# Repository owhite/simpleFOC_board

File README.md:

# Clone your repo (if you don’t already have it locally)
git clone https://github.com/owhite/simpleFOC_board.git

cd simpleFOC_board

# Make sure you have the latest tags
git fetch --tags

# Check out the tag you want
git checkout jlcpcb-order-Y34-4852697

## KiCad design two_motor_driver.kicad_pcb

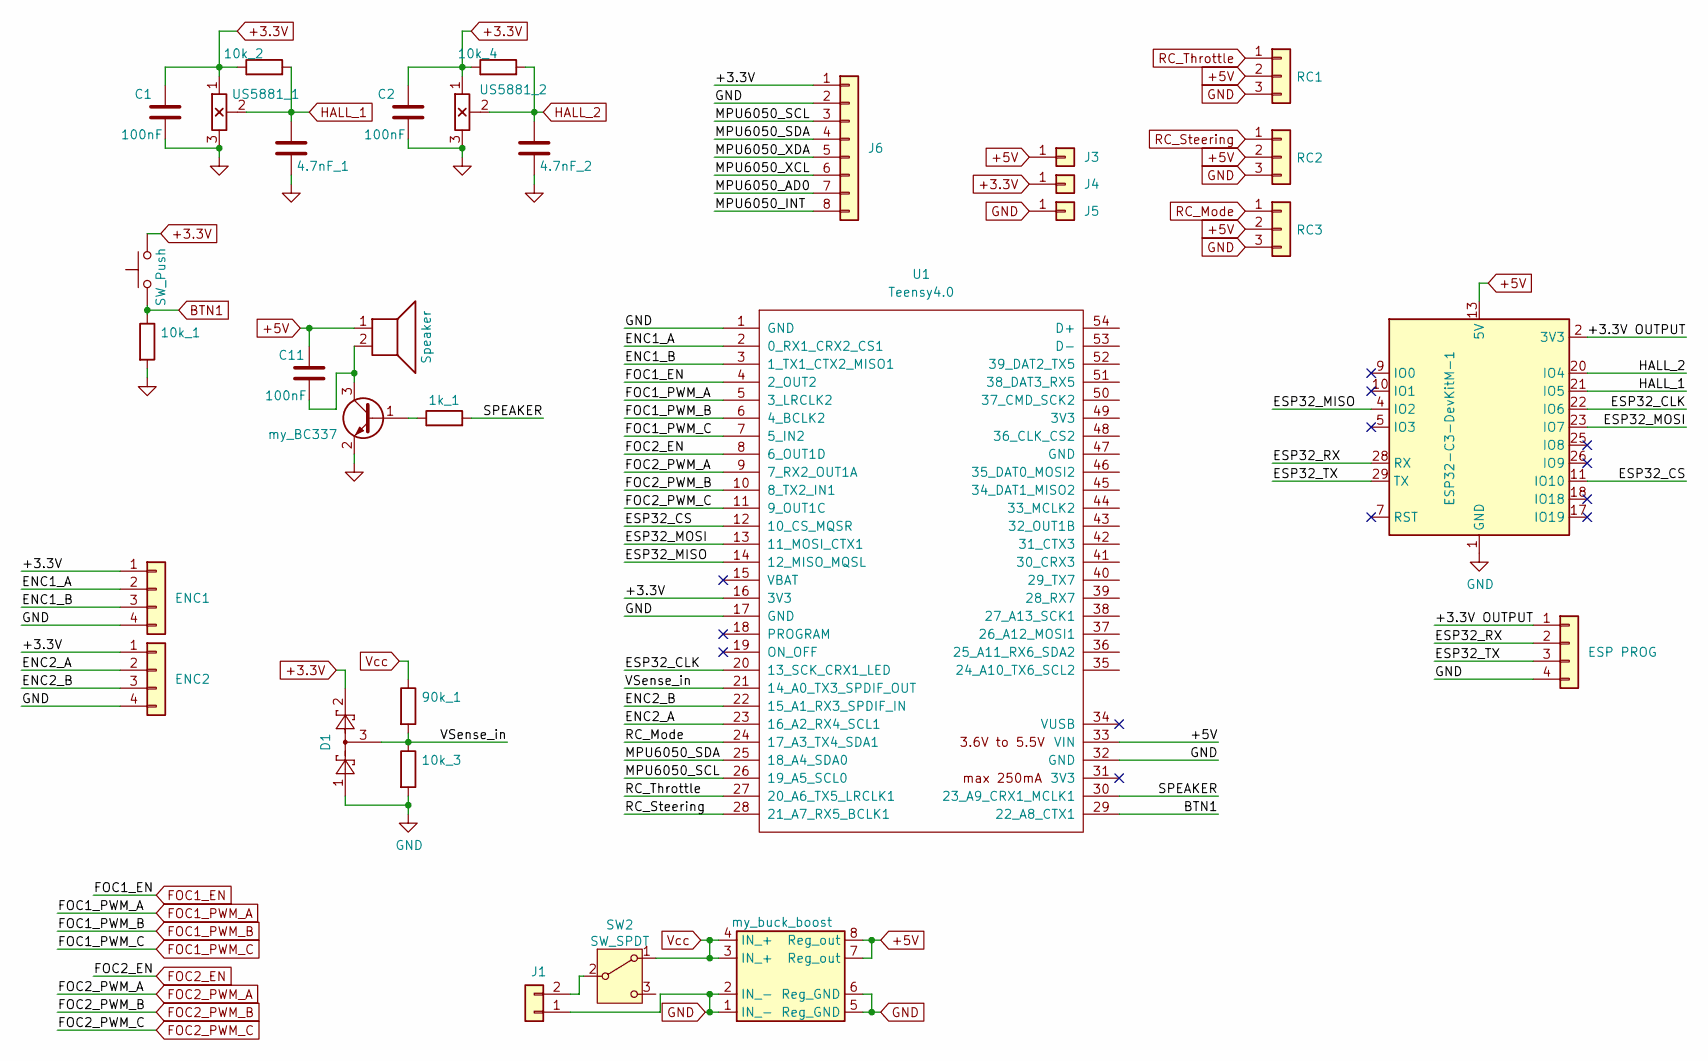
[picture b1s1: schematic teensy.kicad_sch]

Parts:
1k_1, 10k_1, 10k_2, 10k_3, 10k_4: 10k; R_0805_2012Metric
4.7nF_1, 4.7nF_2: 4.7nF; C_0805_2012Metric
90k_1: 90k; R_0805_2012Metric
C1, C2, C11: 100nF; C_0805_2012Metric
D1: BAT54S; SOT-23-3
ENC1, ENC2: J1; PinSocket_1x04_P2.54mm_Vertical
J1: Conn_01x02; PinHeader_1x02_P2.54mm_Vertical
J2: ESP PROG; PinSocket_1x04_P2.54mm_Vertical
J3, J4, J5: Conn_01x01; PinSocket_1x01_P2.54mm_Vertical
J6: Conn_01x08; PinSocket_1x08_P2.54mm_Vertical
LS1: Speaker; SPKR_CDS-13138-SMT-TR
Q2: my_BC337; SOT-23
RC1, RC2, RC3: Conn_01x03; PinHeader_1x03_P2.54mm_Vertical
SW1: SW_Push; SW_Push_SPST_NO_Alps_SKRK
SW2: SW_SPDT; SW_NKK_BB15AH
U1: Teensy4.0; Teensy40
U2: ESP32-C3-DevKitM-1
U5: my_buck_boost
US5881_1, US5881_2: hall_effect_three_wire; PinHeader_1x03_P2.54mm_Vertical

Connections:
+3.3V: 10k_2.1, 10k_4.1, C1.1, C2.1, D1.2, ENC1.1, ENC2.1, J4.1, J6.1, SW1.2, U1.16 (3V3), US5881_1.1 (V+), US5881_2.1 (V+); also elsewhere on the board
+5V: C11.1, J3.1, LS1.1, RC1.2, RC2.2, RC3.2, U1.33 (VIN), U2.13 (5V), U2.14 (5V), U5.7 (Reg_out), U5.8 (Reg_out)
/teensy/+3.3V OUTPUT: J2.1, U2.2 (3V3), U2.3 (3V3)
/teensy/ENC1_A: ENC1.2, U1.2 (0_RX1_CRX2_CS1)
/teensy/ENC1_B: ENC1.3, U1.3 (1_TX1_CTX2_MISO1)
/teensy/ENC2_A: ENC2.2, U1.23 (16_A2_RX4_SCL1)
/teensy/ENC2_B: ENC2.3, U1.22 (15_A1_RX3_SPDIF_IN)
/teensy/ESP32_CLK: U1.20 (13_SCK_CRX1_LED), U2.22 (IO6)
/teensy/ESP32_CS: U1.12 (10_CS_MQSR), U2.11 (IO10)
/teensy/ESP32_MISO: U1.14 (12_MISO_MQSL), U2.4 (IO2)
/teensy/ESP32_MOSI: U1.13 (11_MOSI_CTX1), U2.23 (IO7)
/teensy/ESP32_RX: J2.2, U2.28 (RX)
/teensy/ESP32_TX: J2.3, U2.29 (TX)
/teensy/MPU6050_AD0: J6.7
/teensy/MPU6050_INT: J6.8
/teensy/MPU6050_SCL: J6.3, U1.26 (19_A5_SCL0)
/teensy/MPU6050_SDA: J6.4, U1.25 (18_A4_SDA0)
/teensy/MPU6050_XCL: J6.6
/teensy/MPU6050_XDA: J6.5
/teensy/SPEAKER: 1k_1.2, U1.30 (23_A9_CRX1_MCLK1)
/teensy/VSense_in: 10k_3.1, 90k_1.2, D1.3, U1.21 (14_A0_TX3_SPDIF_OUT)
BTN1: 10k_1.1, SW1.1, U1.29 (22_A8_CTX1)
FOC1_EN: U1.4 (2_OUT2); also elsewhere on the board
FOC1_PWM_A: U1.5 (3_LRCLK2); also elsewhere on the board
FOC1_PWM_B: U1.6 (4_BCLK2); also elsewhere on the board
FOC1_PWM_C: U1.7 (5_IN2); also elsewhere on the board
FOC2_EN: U1.8 (6_OUT1D); also elsewhere on the board
FOC2_PWM_A: U1.9 (7_RX2_OUT1A); also elsewhere on the board
FOC2_PWM_B: U1.10 (8_TX2_IN1); also elsewhere on the board
FOC2_PWM_C: U1.11 (9_OUT1C); also elsewhere on the board
GND: 4.7nF_1.2, 4.7nF_2.2, 10k_1.2, 10k_3.2, C1.2, C2.2, D1.1, ENC1.4, ENC2.4, J1.1, J2.4, J5.1, J6.2, Q2.2 (E), RC1.3, RC2.3, RC3.3, U1.1 (GND), U1.17 (GND), U1.32 (GND), U2.1 (GND), U2.6 (GND), U2.8 (GND), U2.12 (GND), U2.15 (GND), U2.16 (GND), U2.19 (GND), U2.24 (GND), U2.27 (GND), U2.30 (GND), U5.1 (IN_-), U5.2 (IN_-), U5.5 (Reg_GND), U5.6 (Reg_GND), US5881_1.3 (V-), US5881_2.3 (V-); also elsewhere on the board
HALL_1: 4.7nF_1.1, 10k_2.2, U2.21 (IO5), US5881_1.2 (out)
HALL_2: 4.7nF_2.1, 10k_4.2, U2.20 (IO4), US5881_2.2 (out)
unnamed: J1.2, SW2.2 (B)
unnamed: 1k_1.1, Q2.1 (B)
unnamed: C11.2, LS1.2, Q2.3 (C)
RC_Mode: RC3.1, U1.24 (17_A3_TX4_SDA1)
RC_Steering: RC2.1, U1.28 (21_A7_RX5_BCLK1)
RC_Throttle: RC1.1, U1.27 (20_A6_TX5_LRCLK1)
Vcc: 90k_1.1, SW2.1 (A), U5.3 (IN_+), U5.4 (IN_+); also elsewhere on the board

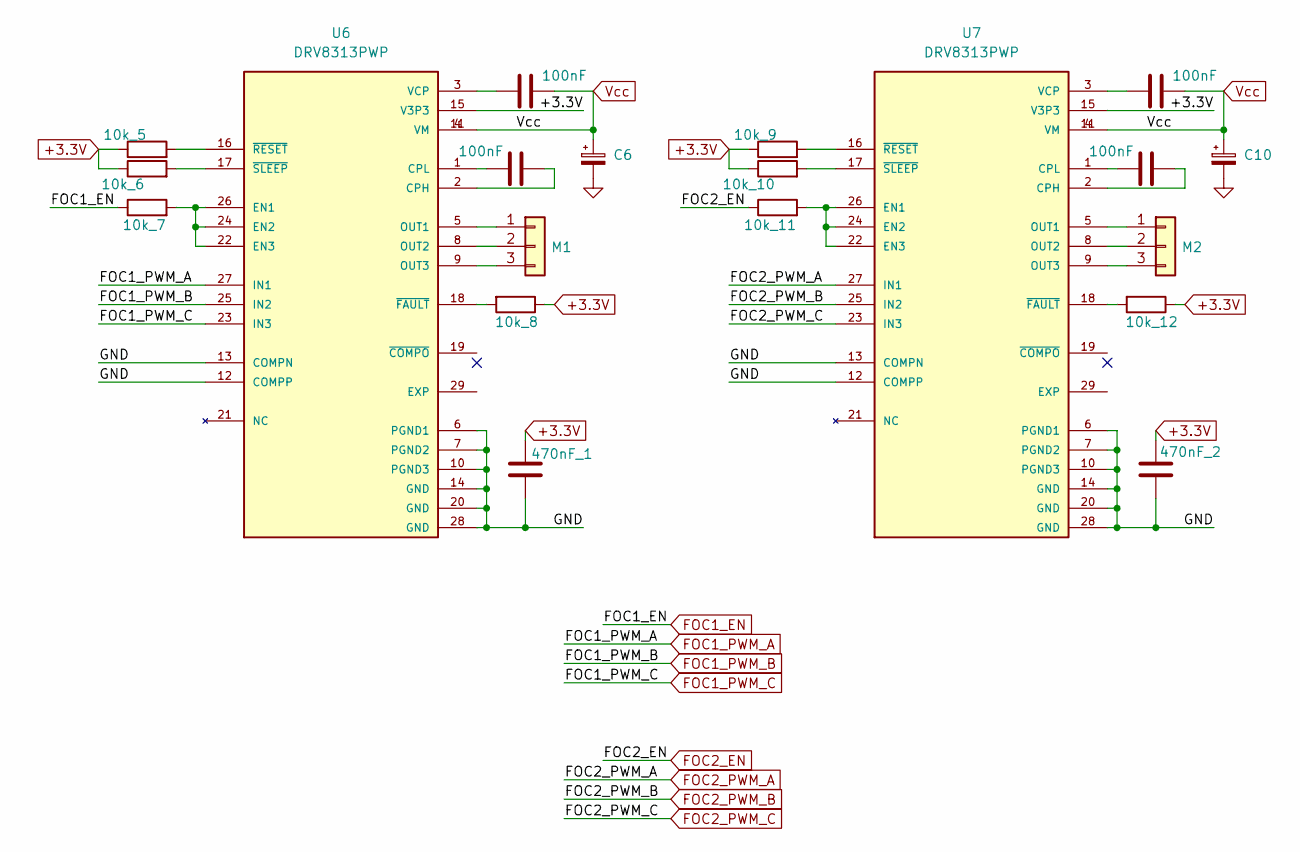
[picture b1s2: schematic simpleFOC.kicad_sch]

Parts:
10k_5, 10k_6, 10k_8, 10k_9, 10k_10, 10k_11, 10k_12: 10k; R_0805_2012Metric
10k_7: 10k; R_0603_1608Metric
470nF_1, 470nF_2: 470nF; C_0805_2012Metric
C3, C4, C7, C8: 100nF; C_0805_2012Metric
C6, C10: C_Polarized_Small; CAP-SMD_BD6.3-L6.6-W6.6-FD
M1, M2: Conn_01x03; PinHeader_1x03_P2.54mm_Vertical
U6, U7: DRV8313PWP; SOP65P640X120-29N; PARTREV D

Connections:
+3.3V: 10k_5.1, 10k_6.1, 10k_8.1, 10k_9.1, 10k_10.1, 10k_12.1, 470nF_1.2, 470nF_2.2, U6.15 (V3P3), U7.15 (V3P3); also elsewhere on the board
FOC1_EN: 10k_7.1; also elsewhere on the board
FOC1_PWM_A: U6.27 (IN1); also elsewhere on the board
FOC1_PWM_B: U6.25 (IN2); also elsewhere on the board
FOC1_PWM_C: U6.23 (IN3); also elsewhere on the board
FOC2_EN: 10k_11.1; also elsewhere on the board
FOC2_PWM_A: U7.27 (IN1); also elsewhere on the board
FOC2_PWM_B: U7.25 (IN2); also elsewhere on the board
FOC2_PWM_C: U7.23 (IN3); also elsewhere on the board
GND: 470nF_1.1, 470nF_2.1, C6.2, C10.2, U6.6 (PGND1), U6.7 (PGND2), U6.10 (PGND3), U6.12 (COMPP), U6.13 (COMPN), U6.14 (GND), U6.20 (GND), U6.28 (GND), U7.6 (PGND1), U7.7 (PGND2), U7.10 (PGND3), U7.12 (COMPP), U7.13 (COMPN), U7.14 (GND), U7.20 (GND), U7.28 (GND); also elsewhere on the board
unnamed: M1.1, U6.5 (OUT1)
unnamed: M1.2, U6.8 (OUT2)
unnamed: M1.3, U6.9 (OUT3)
unnamed: M2.1, U7.5 (OUT1)
unnamed: M2.2, U7.8 (OUT2)
unnamed: M2.3, U7.9 (OUT3)
unnamed: C3.2, U6.2 (CPH)
unnamed: C3.1, U6.1 (CPL)
unnamed: 10k_7.2, U6.22 (EN3), U6.24 (EN2), U6.26 (EN1)
unnamed: C4.1, U6.3 (VCP)
unnamed: 10k_8.2, U6.18 (~FAULT)
unnamed: 10k_5.2, U6.16 (~RESET)
unnamed: 10k_6.2, U6.17 (~SLEEP)
unnamed: C7.2, U7.2 (CPH)
unnamed: C7.1, U7.1 (CPL)
unnamed: 10k_11.2, U7.22 (EN3), U7.24 (EN2), U7.26 (EN1)
unnamed: C8.1, U7.3 (VCP)
unnamed: 10k_12.2, U7.18 (~FAULT)
unnamed: 10k_9.2, U7.16 (~RESET)
unnamed: 10k_10.2, U7.17 (~SLEEP)
Vcc: C4.2, C6.1, C8.2, C10.1, U6.4 (VM), U6.11 (VM), U7.4 (VM), U7.11 (VM); also elsewhere on the board

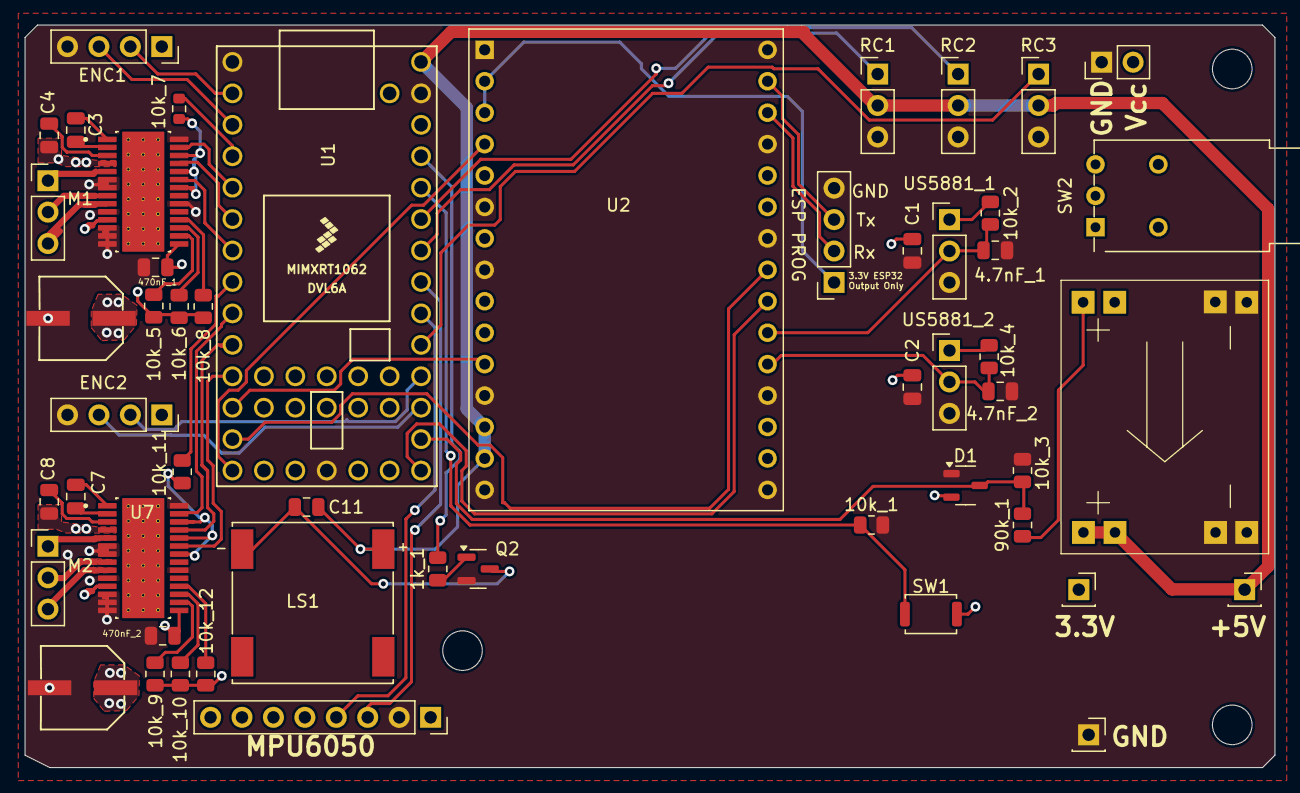
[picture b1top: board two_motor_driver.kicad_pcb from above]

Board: 4 copper layers, 101.0 x 60.0 mm, 52 parts (0 on the bottom side), 56 nets.

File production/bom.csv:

Designator,Footprint,Quantity,Value,LCSC Part #
"10K_1, 10K_10, 10K_11, 10K_12, 10K_2, 10K_3, 10K_4, 10K_5, 10K_6, 10K_8, 10K_9, 1K_1",0805,12,10k,
10K_7,0603,1,10k,
"4.7NF_1, 4.7NF_2",0805,2,4.7nF,
"470NF_1, 470NF_2",0805,2,470nF,
90K_1,0805,1,90k,
"C1, C11, C2, C3, C4, C7, C8",0805,7,100nF,
"C10, C6",CAP-SMD_BD6.3-L6.6-W6.6-FD,2,C_Polarized_Small,
D1,SOT-23-3,1,BAT54S,
"ENC1, ENC2",PinSocket_1x04_P2.54mm_Vertical,2,J1,
J1,PinHeader_1x02_P2.54mm_Vertical,1,Conn_01x02,
J2,PinSocket_1x04_P2.54mm_Vertical,1,ESP PROG,
"J3, J4, J5",PinSocket_1x01_P2.54mm_Vertical,3,Conn_01x01,
J6,PinSocket_1x08_P2.54mm_Vertical,1,Conn_01x08,
LS1,SPKR_CDS-13138-SMT-TR,1,Speaker,
"M1, M2, RC1, RC2, RC3",PinHeader_1x03_P2.54mm_Vertical,5,Conn_01x03,
Q2,SOT-23,1,my_BC337,
SW1,SW_Push_SPST_NO_Alps_SKRK,1,SW_Push,
SW2,SW_NKK_BB15AH,1,SW_SPDT,
U1,Teensy40,1,Teensy4.0,
U2,ESP32-C3-DevKitM-1,1,ESP32-C3-DevKitM-1,
U5,my_buck_boost,1,my_buck_boost,
"U6, U7",SOP65P640X120-29N,2,DRV8313PWP,
"US5881_1, US5881_2",PinHeader_1x03_P2.54mm_Vertical,2,hall_effect_three_wire,

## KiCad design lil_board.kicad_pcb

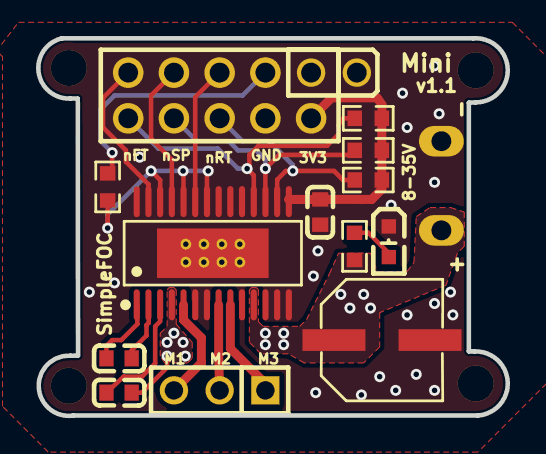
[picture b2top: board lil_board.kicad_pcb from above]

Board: 2 copper layers, 26.1 x 21.0 mm, 20 parts (0 on the bottom side), 18 nets.

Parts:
C1, C2: 100nF; C0603
C3: 100uF; CAP-SMD_BD6.3-L6.6-W6.6-FD
C4: 470nF; C0603
H1: Female header2.54mm2*5p Straight; HDR-TH_10P-P2.54-V-F-R2-C5-S2.54
LED1: 19-213/Y2C-CQ2R2L/3T(CY); LED0603-R-RD
P1: Header-Female-2.54_1x3; HDR-TH_3P-P2.54-V-F
Pad_gge5124: Pad_gge5124
Pad_gge5154: Pad_gge5154
Pad_gge5250: Pad_gge5250
Pad_gge5325: Pad_gge5325
Pad_gge5349: Pad_gge5349
Pad_gge7437: Pad_gge7437
Pad_gge9415: Pad_gge9415
R1, R2, R3, R4: 10kΩ; R0603
R5: 1kΩ; R0603
U1: DRV8313PWPR; HTSSOP-28_L9.8-W4.5-P0.65-LS6.6-BL-EP

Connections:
3.3V: C4.2, H1.2, R1.1, R2.1, R3.1, U1.15
EN: R4.2, U1.22, U1.24, U1.26
GND: C3.2, C4.1, H1.1, H1.4, LED1.2, Pad_gge5124.2, Pad_gge5250.5, Pad_gge5325.5, Pad_gge5349.5, Pad_gge7437.5, Pad_gge9415.1, U1.6, U1.7, U1.10, U1.12, U1.13, U1.14, U1.20, U1.28, U1.29
IN1: H1.9, U1.27
IN3: H1.5, U1.23
LED1_1: LED1.1, R5.2
NFLT: H1.10, R1.2, U1.18
NRES: H1.6, R3.2, U1.16
NSLP: H1.8, R2.2, U1.17
R4_1: H1.3, R4.1
U1_1: C1.2, U1.1
U1_2: C1.1, U1.2
U1_3: C2.2, U1.3
U1_5: P1.3, U1.5
U1_8: P1.2, U1.8
U1_9: P1.1, U1.9
U1_25: H1.7, U1.25
VCC: C2.1, C3.1, Pad_gge5154.3, R5.1, U1.4, U1.11

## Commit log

2025-07-07 initialize
2025-07-08 pcb layout
2025-07-08 Add .gitignore for KiCad project
2025-07-08 Remove ignored files from repo
2025-07-17 converted to teensy 4.0
2025-07-18 started layout
2025-07-18 completing traces
2025-07-20 added DRV8313
2025-07-21 jlcpcb order Y34-4852697
2025-07-21 added README
